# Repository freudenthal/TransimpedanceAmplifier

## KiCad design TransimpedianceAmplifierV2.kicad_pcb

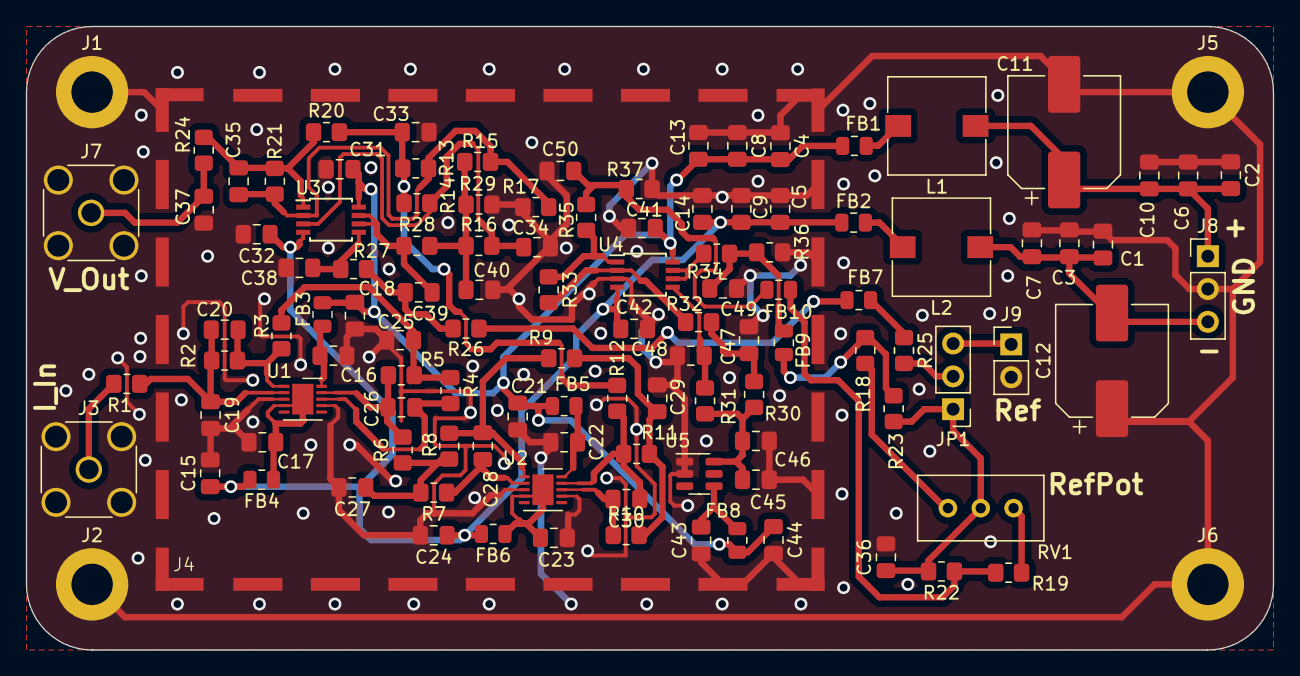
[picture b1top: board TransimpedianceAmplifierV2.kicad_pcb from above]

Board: 2 copper layers, 96.5 x 48.3 mm, 115 parts (0 on the bottom side), 50 nets.

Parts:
C1, C2, C4, C5, C16, C17, C22, C23, C31, C32, C36, C38, C39, C40, C41, C42, C43, C47, C48, C49, C50: 0.1uF; C_0805_2012Metric_Pad1.18x1.45mm_HandSolder
C3, C6, C8, C9, C15, C18, C21, C24, C44, C45: 1uF; C_0805_2012Metric_Pad1.18x1.45mm_HandSolder
C7, C10, C13, C14, C46: 10uF; C_0805_2012Metric_Pad1.18x1.45mm_HandSolder
C11, C12: 100uF; CP_Elec_8x10.5
C19, C20, C25, C26, C27, C28, C29, C30, C33, C34, C35, C37: 4pF; C_0805_2012Metric_Pad1.18x1.45mm_HandSolder
FB1, FB2, FB3, FB4, FB5, FB6, FB7, FB8, FB9, FB10: FerriteBead; R_0805_2012Metric
J1, J2, J5, J6: Screw_Terminal_01x01; MountingHole_3.2mm_M3_DIN965_Pad
J3: CurrentIn; SMA_Amphenol_132134_Vertical
J4: RFShield; BMI-S-230-F-R
J7: VoltageOut; SMA_Amphenol_132134_Vertical
J8: Vin; PinHeader_1x03_P2.54mm_Vertical
J9: OffsetIn; PinHeader_1x02_P2.54mm_Vertical
JP1: OffsetInPot; PinHeader_1x03_P2.54mm_Vertical
L1, L2: 100uH; L_Wuerth_WE-PD-Typ-7345
R1: 20Ω; R_0805_2012Metric_Pad1.20x1.40mm_HandSolder
R2, R12, R18, R19, R24, R25, R28, R34, R35: 1kΩ; R_0805_2012Metric_Pad1.20x1.40mm_HandSolder
R3, R4, R6, R7, R9, R10: 200Ω; R_0805_2012Metric_Pad1.20x1.40mm_HandSolder
R5, R8, R11: 2kΩ; R_0805_2012Metric_Pad1.20x1.40mm_HandSolder
R13, R16, R20: 1kΩ+; R_0805_2012Metric_Pad1.20x1.40mm_HandSolder
R14, R15, R17, R21: 1kΩ-; R_0805_2012Metric_Pad1.20x1.40mm_HandSolder
R22, R23, R26, R27, R30, R31, R32, R33: 10kΩ; R_0805_2012Metric_Pad1.20x1.40mm_HandSolder
R29, R36, R37: 100kΩ; R_0805_2012Metric_Pad1.20x1.40mm_HandSolder
RV1: 10kΩ; Potentiometer_Bourns_3296W_Vertical
U1, U2: LTC6269xDD; DFN-10-1EP_3x3mm_P0.5mm_EP1.65x2.38mm
U3, U4: MAX44246; TSSOP-8_3x3mm_P0.65mm
U5: LT6654-1.25; TSOT-23-6

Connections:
/OutputOffset/Input: C33.2, R12.1, R13.1, R14.1, R20.2
/OutputOffset/Output: C37.1, J7.1, R24.2
/OutputOffset/Vref: C40.2, R15.1, R16.1, R28.2, R29.2
/OutputOffset/Vref+: FB9.2, R18.1, R23.1
/OutputOffset/Vref-: FB10.2, R19.1, R22.1
/TransimpedanceFrontEnd/Input: J3.1, R1.1
GND: C1.2, C2.1, C3.2, C4.1, C5.1, C6.1, C7.2, C8.1, C9.1, C10.1, C11.2, C12.1, C13.1, C14.1, C15.2, C16.1, C17.2, C18.2, C19.2, C21.2, C22.1, C23.2, C24.2, C25.2, C27.2, C29.2, C31.1, C32.2, C33.1, C34.2, C36.2, C37.2, C38.1, C40.1, C41.1, C42.2, C43.1, C44.2, C45.1, C46.1, C47.1, C48.1, C49.1, C50.1, J1.1, J2.1, J3.2, J4.1 (Shield), J5.1, J6.1, J7.2, J8.2, J9.2, R17.2, R29.1, R36.1, R37.1, U1.3 (+), U1.7 (+), U2.3 (+), U2.7 (+), U4.3 (+), U5.1 (GND), U5.2 (GND)
unnamed: C17.1, FB4.1, U1.4 (V-), U1.11 (V-)
unnamed: C20.1, R2.1, R3.2, U1.1
unnamed: C23.1, FB6.1, U2.4 (V-), U2.11 (V-)
unnamed: C25.1, R3.1, R4.2, R5.2
unnamed: C26.1, R5.1, R6.2, U1.9
unnamed: C27.1, R6.1, R7.2, R8.2
unnamed: C28.1, R8.1, R9.2, U2.1
unnamed: C29.1, R9.1, R10.2, R11.2
unnamed: C30.1, R11.1, R12.2, U2.9
unnamed: C35.1, R20.1, R21.1, R24.1, U3.1
unnamed: C39.2, R26.1, R27.2
unnamed: C47.2, R30.1, R32.2
unnamed: C49.2, FB9.1, R34.2, R36.2
unnamed: C50.2, FB10.1, R35.2, R37.2
unnamed: FB1.2, L1.2
unnamed: FB2.2, L2.2
unnamed: FB7.1, R25.1
unnamed: FB7.2, R26.2
unnamed: C2.2, C6.2, C10.2, C11.1, J8.1, L1.1
unnamed: C1.1, C3.1, C7.1, C12.2, J8.3, L2.1
unnamed: J9.1, JP1.3 (B)
unnamed: C36.1, JP1.1 (A), R22.2, R23.2, RV1.2
unnamed: JP1.2 (C), R25.2
unnamed: R18.2, RV1.1
unnamed: R19.2, RV1.3
unnamed: R33.1, R35.1, U4.1
unnamed: C19.1, C20.2, R1.2, R2.2, U1.2 (-)
unnamed: C26.2, R4.1, U1.8 (-)
unnamed: C16.2, FB3.2, U1.10 (V+)
unnamed: C28.2, R7.1, U2.2 (-)
unnamed: C30.2, R10.1, U2.8 (-)
unnamed: C22.2, FB5.2, U2.10 (V+)
unnamed: C34.1, R14.2, R16.2, U3.3 (+)
unnamed: C35.2, R13.2, R15.2, R17.1, R21.2, U3.2 (-)
unnamed: C38.2, R27.1, U3.5 (+)
unnamed: C39.1, R28.1, U3.6 (-), U3.7
unnamed: R32.1, R33.2, U4.2 (-)
unnamed: C48.2, R31.1, U4.5 (+)
unnamed: R34.1, U4.6 (-), U4.7
unnamed: C43.2, FB8.2, U5.4 (Vin)
unnamed: C45.2, C46.2, R30.2, R31.2, U5.6 (Vout)
VDD: C4.2, C8.2, C13.2, C18.1, C21.1, C31.2, C41.2, C44.1, FB1.1, FB3.1, FB5.1, FB8.1, U3.8 (V+), U4.8 (V+)
VSS: C5.2, C9.2, C14.2, C15.1, C24.1, C32.1, C42.1, FB2.1, FB4.2, FB6.2, U3.4 (V-), U4.4 (V-)

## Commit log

2023-08-27 Initial commit.
